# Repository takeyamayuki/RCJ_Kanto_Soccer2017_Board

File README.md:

# RCJ_Kanto_Soccer2017_Board
ロボカップジュニア2017関東大会に出場したチームNTKのKicad基板データ  

ロボットの動作状況は以下のYoutube再生リストから確認できます。  
https://www.youtube.com/playlist?list=PLkEBRGnKNUILFJv4zKvQkQi69NoT-_FYg

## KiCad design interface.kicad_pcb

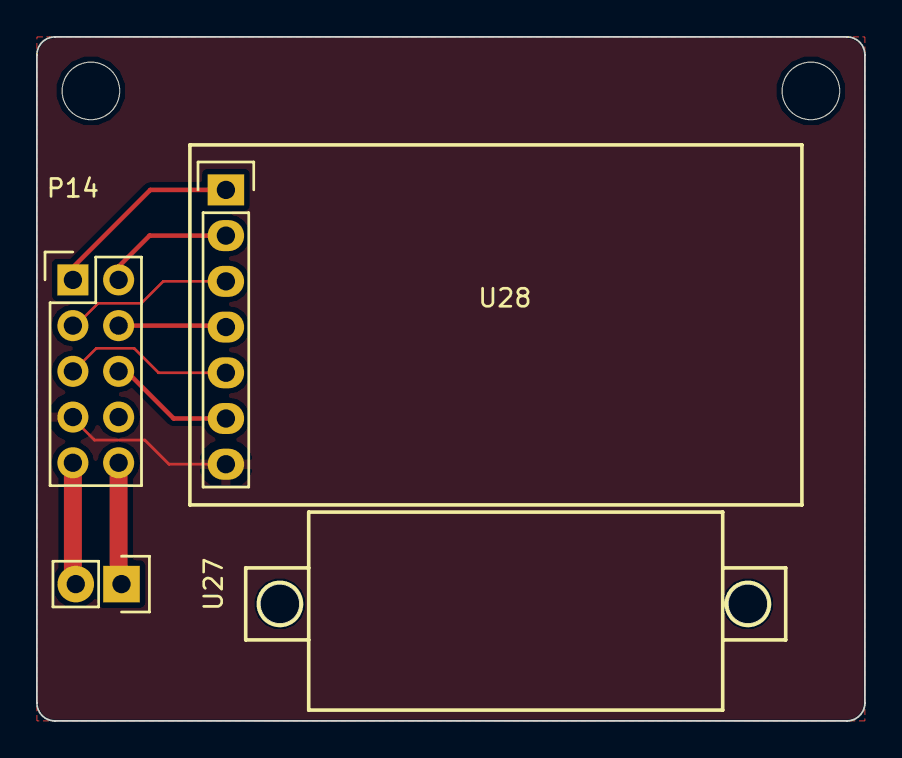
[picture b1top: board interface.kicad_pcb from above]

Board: 2 copper layers, 46.0 x 38.0 mm, 3 parts (0 on the bottom side), 9 nets.

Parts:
P14: CONN_01X10; Pin_Header_Straight_2x05
U27: DCV-meter; Pin_Header_Straight_1x02
U28: AQM1248A; Socket_Strip_Straight_1x07

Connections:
unnamed: P14.1, U28.1
unnamed: P14.2, U28.2
unnamed: P14.3, U28.3
unnamed: P14.4, U28.4
unnamed: P14.5, U28.5
unnamed: P14.6, U28.6
unnamed: P14.7, U28.7
unnamed: P14.9, U27.2
unnamed: P14.10, U27.1

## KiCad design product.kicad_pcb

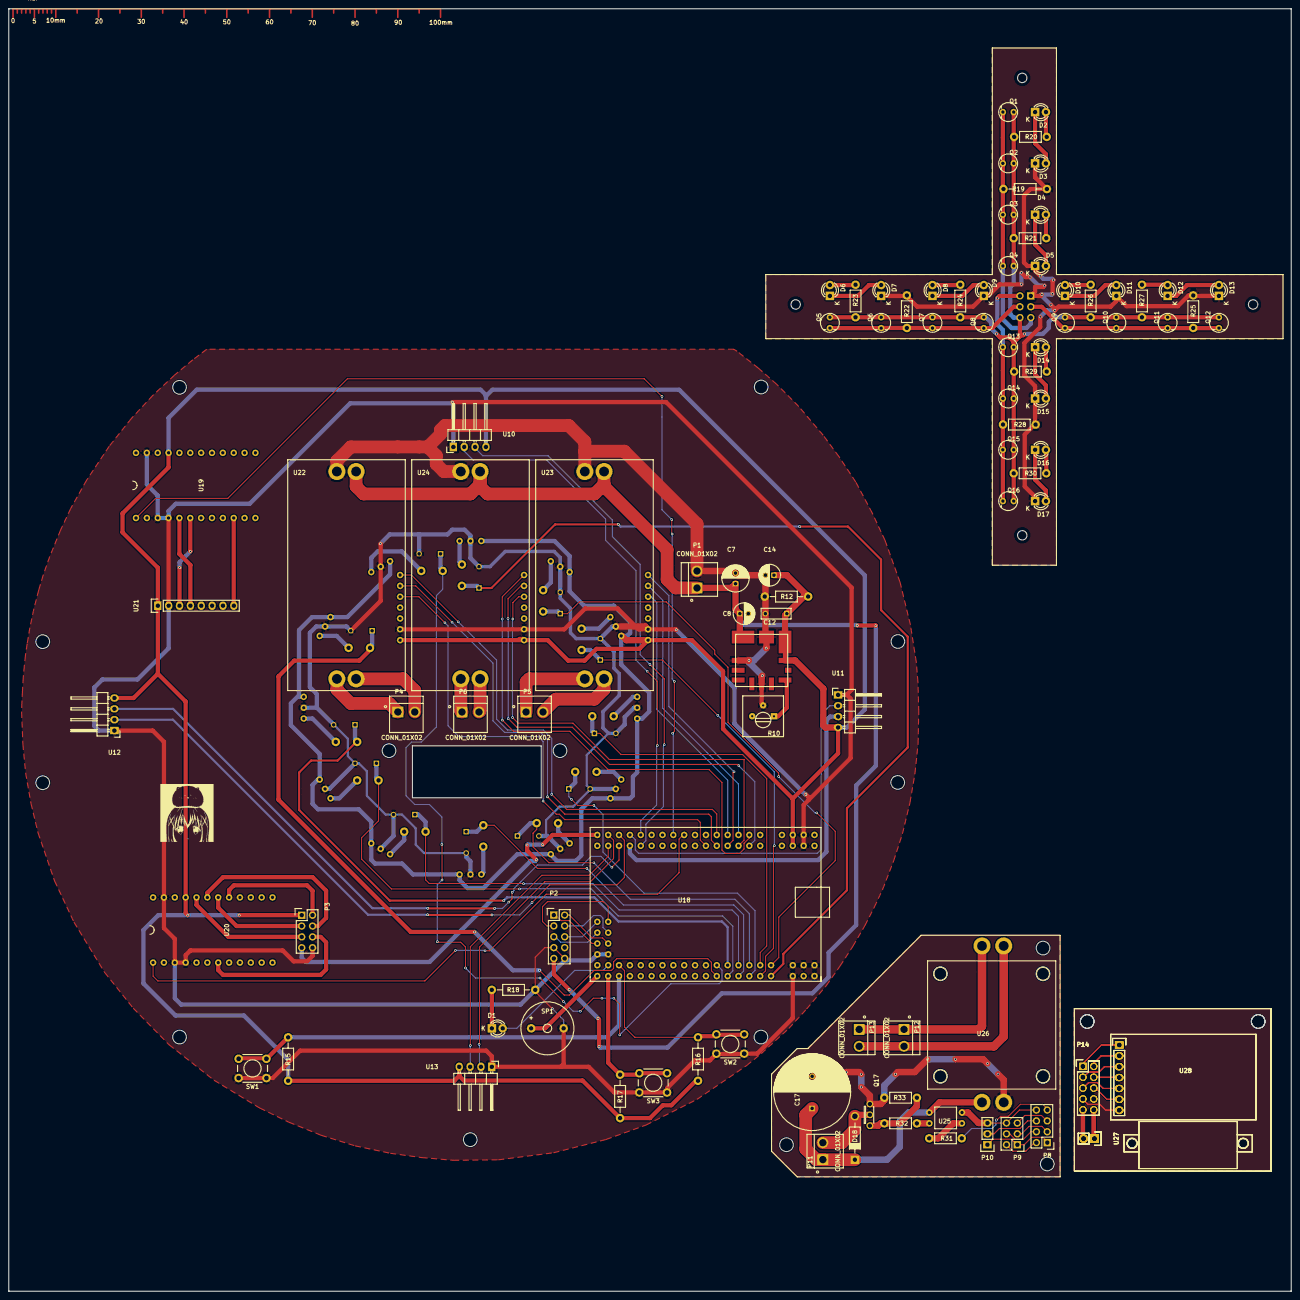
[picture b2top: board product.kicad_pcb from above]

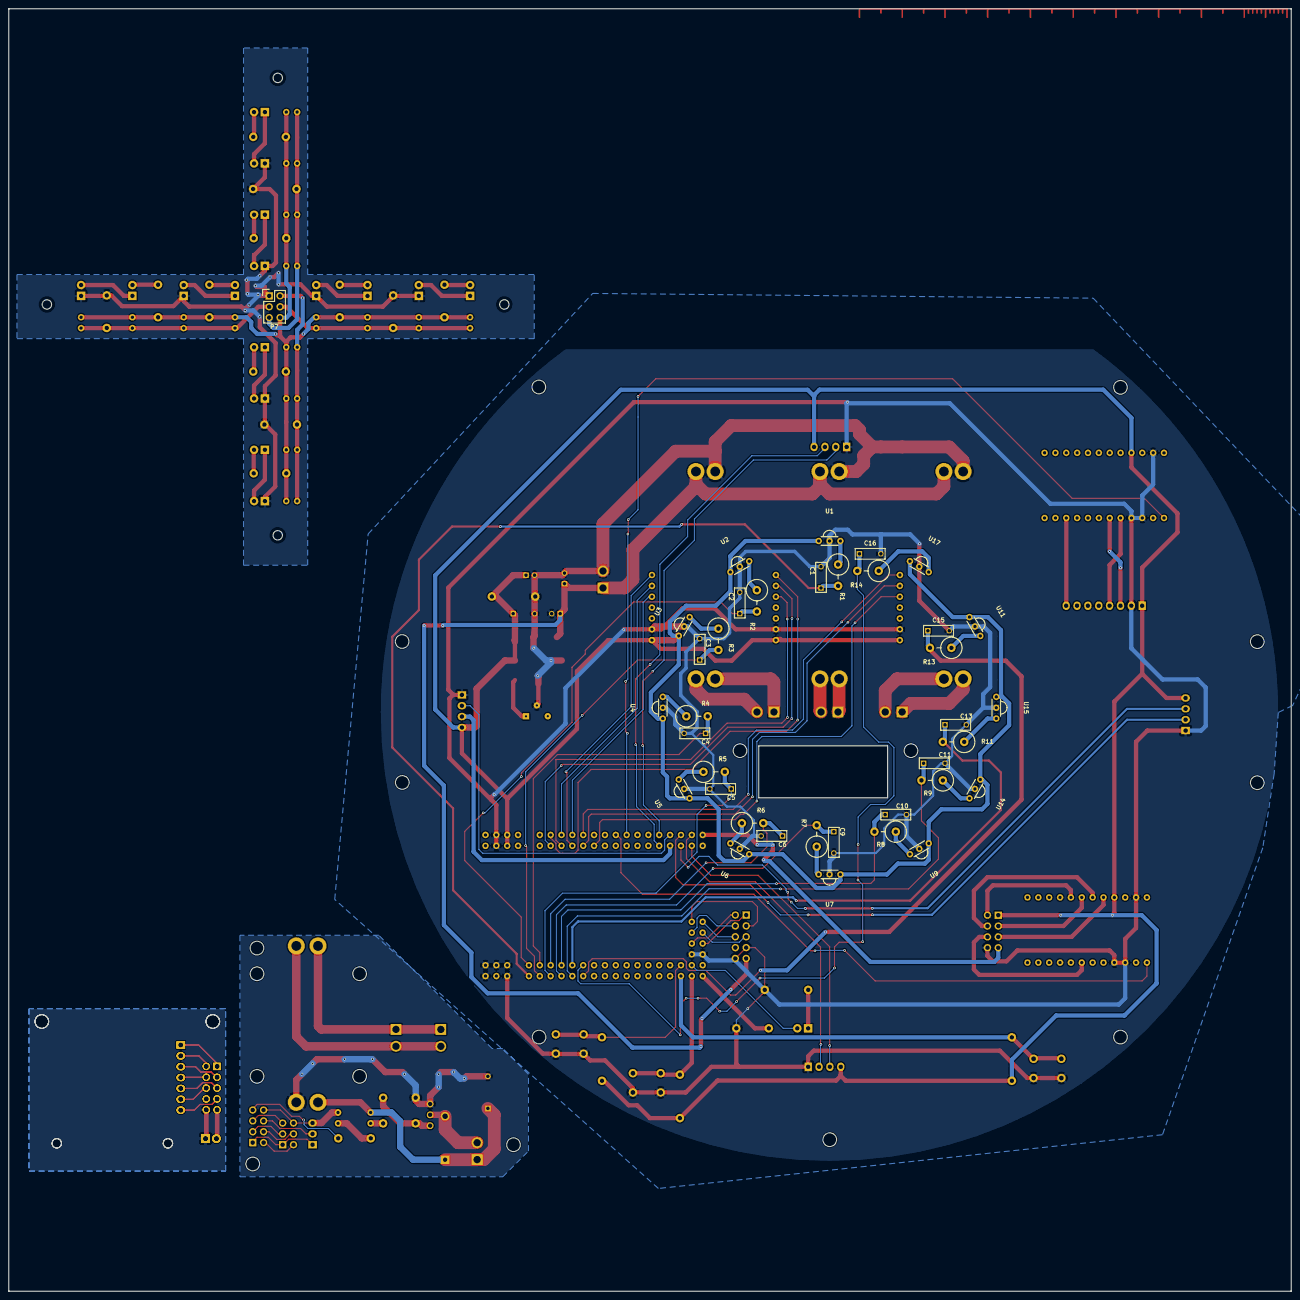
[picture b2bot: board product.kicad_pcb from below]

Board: 2 copper layers, 300.0 x 300.0 mm, 134 parts (37 on the bottom side), 122 nets.

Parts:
C1, C2, C3, C4, C5, C6, C9, C10, C11, C13, C15, C16: 1u; C_Rect_L7_W2.5_P5
C7: 220u; C_Radial_D6.3_L11.2_P2.5
C8: 22u; C_Radial_D5_L11_P2
C12: 10u; C_Rect_L7_W2.5_P5
C14: 100u; C_Radial_D5_L11_P2
C17: 2200u; C_Radial_D18_L36_P7.5
D1, D2, D3, D4, D5, D6, D7, D8, D9, D10, D11, D12, D13, D14, D15, D16, D17: LED; LED-3MM
D18: 1N4007; Diode_DO-41_SOD81_Horizontal_RM10
P1, P4, P5, P6, P11, P12, P13: CONN_01X02; JST_B2P-VH(LF)(SN)
P2, P14, P14#2: CONN_01X10; Pin_Header_Straight_2x05
P3, P8: CONN_01X08; Pin_Header_Straight_2x04
P7, P9: CONN_01X06; Pin_Header_Straight_2x03
P10: CONN_01X03; Pin_Header_Straight_1x03
Q1, Q2, Q3, Q4, Q5, Q6, Q7, Q8, Q9, Q10, Q11, Q12, Q13, Q14, Q15, Q16: NJL7502L; NJL7502
Q17: IRFB3607
R1, R2, R3, R4, R5, R6, R7, R8, R9, R11, R13, R14: 100k; Resistor_Vertical_RM5mm
R10: 5k; Potentiometer_Trimmer-Suntan-TSR-3386P
R12: 1.2k; Resistor_Horizontal_RM10mm
R15, R16, R17, R19: 10k; Resistor_Horizontal_RM10mm
R18: 330; Resistor_Horizontal_RM10mm
R20, R21, R23, R24, R26, R27, R29, R30: 51; Resistor_Horizontal_RM7mm
R22, R25, R28: 10k; Resistor_Horizontal_RM7mm
R31: 330; Resistor_Horizontal_RM7mm
R32, R33: 1k; Resistor_Horizontal_RM7mm
SP1: Buzzer; Buzzer_12x9.5RM7.6
SW1, SW2, SW3: SW_PUSH; SW_PUSH_6mm
U1, U2, U3, U4, U5, U6, U7, U9, U11#2, U14, U15, U17: IRM3638
U8: OKL-T/6-W12N-C; OKL-T-6
U10, U11, U12, U13: HC-SR04; Pin_Header_Angled_1x04
U18: Arduino.MEGA.mini; Arduino_MEGA_mini
U19, U20: Pro_micro
U21: MPU-6050; Pin_Header_Straight_1x08
U22, U23, U24: VNH2SP30
U25: TLP621-1
U26: up_dcdc30V; DCDC-UP
U27, U27#2: DCV-meter; Pin_Header_Straight_1x02
U28, U28#2: AQM1248A; Socket_Strip_Straight_1x07

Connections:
+5V: C12.1, C14.1, P3.1, R12.1, R15.1, R16.1, R17.1, U1.Vcc, U2.Vcc, U3.Vcc, U4.Vcc, U5.Vcc, U6.Vcc, U7.Vcc, U8.4, U8.5, U9.Vcc, U10.4, U11.4, U11#2.Vcc, U12.4, U13.4, U14.Vcc, U15.Vcc, U17.Vcc, U18.Vcc, U19.Vcc, U20.Vcc, U21.1, U22.0, U23.0, U24.0
GND: C1.2, C2.2, C3.2, C4.2, C5.2, C6.2, C7.2, C8.2, C9.2, C10.2, C11.2, C12.2, C13.2, C14.2, C15.2, C16.2, P1.2, P2.7, P2.10, P3.8, R10.2, R12.2, R18.2, SP1.2, SW1.1, SW2.1, SW3.1, U1.GND, U2.GND, U3.GND, U4.GND, U5.GND, U6.GND, U7.GND, U8.1, U8.3, U8.7, U9.GND, U10.1, U11.1, U11#2.GND, U12.1, U13.1, U14.GND, U15.GND, U17.GND, U18.GND, U19.GND, U20.GND, U21.2, U22.1, U22.8, U23.1, U23.8, U24.1, U24.8
unnamed: C1.1, R1.2, U18.A0
unnamed: C2.1, R2.2, U18.A1
unnamed: C3.1, R3.2, U18.A2
unnamed: C4.1, R4.2, U18.A3
unnamed: C5.1, R5.2, U18.A4
unnamed: C6.1, R6.2, U18.A5
unnamed: C9.1, R7.2, U18.A6
unnamed: C10.1, R8.2, U18.A7
unnamed: C11.1, R9.2, U18.A8
unnamed: C13.1, R11.2, U18.A9
unnamed: C15.1, R13.2, U18.A10
unnamed: C16.1, R14.2, U18.A11
unnamed: C17.1, D18.1, P11.1, U25.5, U26.1
unnamed: C17.2, Q17.3, R33.2, U26.2
unnamed: D1.1, R18.1
unnamed: D1.2, U18.45
unnamed: D2.1, D3.2
unnamed: D2.2, R20.2
unnamed: D4.1, D5.2
unnamed: D4.2, R21.2
unnamed: D6.1, D7.2
unnamed: D6.2, R23.2
unnamed: D8.1, D9.2
unnamed: D8.2, R24.2
unnamed: D10.1, D11.2
unnamed: D10.2, R26.2
unnamed: D3.1, D5.1, D7.1, D9.1, D11.1, D13.1, D15.1, D17.1, P7.1, R19.2, R22.2, R25.2, R28.2
unnamed: D12.1, D13.2
unnamed: D12.2, R27.2
unnamed: D14.1, D15.2
unnamed: D14.2, R29.2
unnamed: D16.1, D17.2
unnamed: D16.2, R30.2
unnamed: D18.2, P11.2, Q17.2
unnamed: P2.1, U18.48
unnamed: P2.2, U18.49
unnamed: P2.3, U18.53
unnamed: P2.4, U18.51
unnamed: P2.5, U18.50
unnamed: P2.6, U18.52
unnamed: P3.2, U20.18
unnamed: P3.3, U20.19
unnamed: P3.4, U20.20
unnamed: P3.5, U20.21
unnamed: P3.6, U20.4
unnamed: P3.7, U18.31
unnamed: P4.1, U22.9
unnamed: P4.2, U22.10
unnamed: P5.1, U23.9
unnamed: P5.2, U23.10
unnamed: P6.1, U24.9
unnamed: P6.2, U24.10
unnamed: P7.2, Q13.1, Q14.1, Q15.1, Q16.1, R28.1
unnamed: P7.3, Q9.1, Q10.1, Q11.1, Q12.1, R25.1
unnamed: P7.4, Q5.1, Q6.1, Q7.1, Q8.1, R22.1
unnamed: P7.5, Q1.1, Q2.1, Q3.1, Q4.1, R19.1
unnamed: P7.6, Q1.3, Q2.3, Q3.3, Q4.3, Q5.3, Q6.3, Q7.3, Q8.3, Q9.3, Q10.3, Q11.3, Q12.3, Q13.3, Q14.3, Q15.3, Q16.3, R20.1, R21.1, R23.1, R24.1, R26.1, R27.1, R29.1, R30.1
unnamed: P8.2, P9.2
unnamed: P8.3, P9.3
unnamed: P8.4, P9.4
unnamed: P8.5, P9.5
unnamed: P8.7, R31.1
unnamed: P8.1, P9.1, P10.1
unnamed: P8.6, P10.2
unnamed: P8.8, P9.6, P10.3, U25.2
unnamed: P12.1, P13.1, U26.3
unnamed: P12.2, P13.2, U26.4
unnamed: P14.1, P14#2.1, U28.1, U28#2.1
unnamed: P14.2, P14#2.2, U28.2, U28#2.2
unnamed: P14.3, P14#2.3, U28.3, U28#2.3
unnamed: P14.4, P14#2.4, U28.4, U28#2.4
unnamed: P14.5, P14#2.5, U28.5, U28#2.5
unnamed: P14.6, P14#2.6, U28.6, U28#2.6
unnamed: P14.7, P14#2.7, U28.7, U28#2.7
unnamed: P14.8, P14#2.8
unnamed: P14.9, P14#2.9, U27.2, U27#2.2
unnamed: P14.10, P14#2.10, U27.1, U27#2.1
unnamed: Q17.1, R32.2, R33.1
unnamed: R1.1, U1.OUT
unnamed: R2.1, U2.OUT
unnamed: R3.1, U3.OUT
unnamed: R4.1, U4.OUT
unnamed: R5.1, U5.OUT
unnamed: R6.1, U6.OUT
unnamed: R7.1, U7.OUT
unnamed: R8.1, U9.OUT
unnamed: R9.1, U14.OUT
unnamed: R10.1, U8.6
unnamed: R11.1, U15.OUT
unnamed: R13.1, U11#2.OUT
unnamed: R14.1, U17.OUT
unnamed: R15.2, SW1.2, U18.42
unnamed: R16.2, SW2.2, U18.43
unnamed: R17.2, SW3.2, U18.44
unnamed: R31.2, U25.1
unnamed: R32.1, U25.4
unnamed: SP1.1, U18.46
unnamed: U10.2, U18.23
unnamed: U10.3, U18.22
unnamed: U11.2, U18.25
unnamed: U11.3, U18.24
unnamed: U12.2, U18.27
unnamed: U12.3, U18.26
unnamed: U13.2, U18.29
unnamed: U13.3, U18.28
unnamed: U18.2, U24.5
unnamed: U18.3, U24.6
unnamed: U18.4, U24.4
unnamed: U18.5, U23.5
unnamed: U18.6, U23.6
unnamed: U18.7, U23.4
unnamed: U18.8, U22.5
unnamed: U18.9, U22.6
unnamed: U18.10, U22.4
unnamed: U18.15, U20.1
unnamed: U18.17, U19.1
unnamed: U19.2, U21.4
unnamed: U19.3, U21.3
unnamed: U19.7, U21.8
VSS: C7.1, C8.1, P1.1, P2.9, U8.2, U22.7, U23.7, U24.7

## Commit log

2021-05-19 initial
